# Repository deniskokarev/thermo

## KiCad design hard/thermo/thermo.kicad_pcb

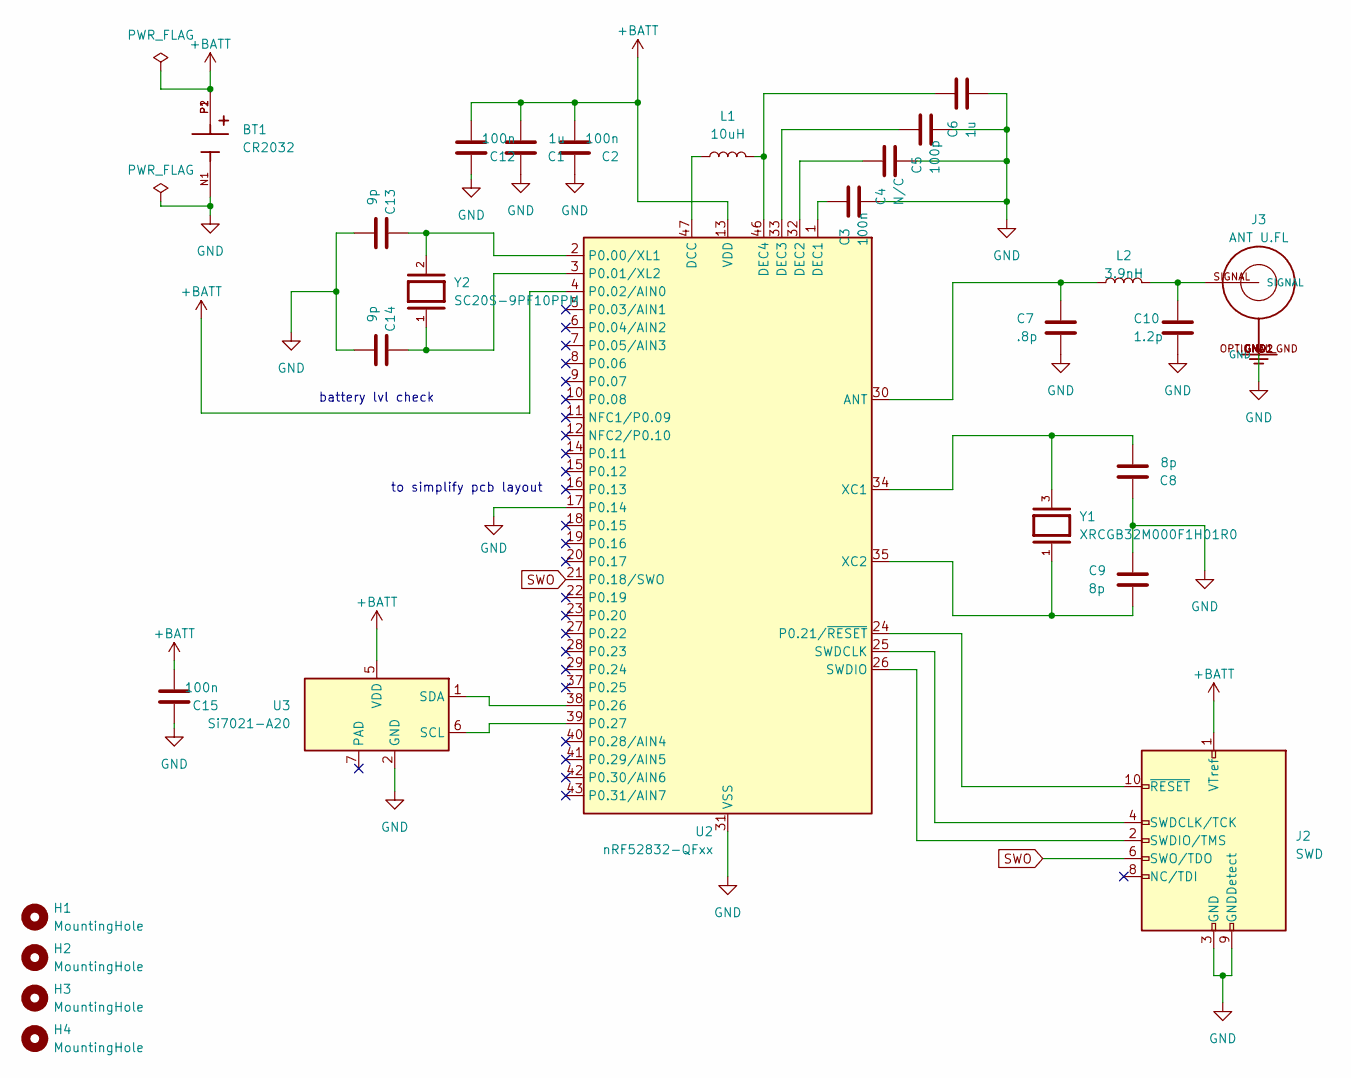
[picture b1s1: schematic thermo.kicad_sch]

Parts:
BT1: CR2032; BAT_BAT-HLD-001
C1, C6: 1u; C_0603_1608Metric_Pad1.08x0.95mm_HandSolder
C2, C3, C12, C15: 100n; C_0603_1608Metric_Pad1.08x0.95mm_HandSolder
C4: N/C; C_0603_1608Metric_Pad1.08x0.95mm_HandSolder
C5: 100p; C_0603_1608Metric_Pad1.08x0.95mm_HandSolder
C7: .8p; C_0603_1608Metric_Pad1.08x0.95mm_HandSolder
C8, C9: 8p; C_0603_1608Metric_Pad1.08x0.95mm_HandSolder
C10: 1.2p; C_0603_1608Metric_Pad1.08x0.95mm_HandSolder
C13, C14: 9p; C_0603_1608Metric_Pad1.08x0.95mm_HandSolder
H1, H2, H3, H4: MountingHole; MountingHole_2.2mm_M2
J2: SWD; PinHeader_2x05_P1.27mm_Vertical_SMD
J3: ANT U.FL; AMPHENOL_A-1JB
L1: 10uH; L_0603_1608Metric_Pad1.05x0.95mm_HandSolder
L2: 3.9nH; L_0603_1608Metric_Pad1.05x0.95mm_HandSolder
U2: nRF52832-QFxx; QFN-48-1EP_6x6mm_P0.4mm_EP4.6x4.6mm
U3: Si7021-A20; DFN-6-1EP_3x3mm_P1mm_EP1.5x2.4mm
Y1: XRCGB32M000F1H01R0; OSC_XRCGB32M000F1H01R0
Y2: SC20S-9PF10PPM; R_1210_3225Metric

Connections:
+BATT: BT1.P1, BT1.P2, C1.1, C2.1, C12.1, C15.1, J2.1 (VTref), U2.4 (P0.02/AIN0), U2.13 (VDD), U2.36 (VDD), U2.48 (VDD), U3.5 (VDD)
GND: BT1.N1, C1.2, C2.2, C3.1, C4.1, C5.1, C6.1, C7.1, C8.2, C9.2, C10.1, C12.2, C13.1, C14.1, C15.2, J2.3 (GND), J2.5 (GND), J2.9 (GNDDetect), J3.GND1 (GND), J3.GND2 (GND), J3.OPTIONAL_GND (GND), U2.17 (P0.14), U2.31 (VSS), U2.45 (VSS), U2.49 (VSS), U3.2 (GND)
unnamed: C10.2, J3.SIGNAL, L2.2
unnamed: J2.4 (SWDCLK/TCK), U2.25 (SWDCLK)
unnamed: J2.2 (SWDIO/TMS), U2.26 (SWDIO)
unnamed: J2.10 (~RESET), U2.24 (P0.21/~RESET)
unnamed: C7.2, L2.1, U2.30 (ANT)
unnamed: L1.1, U2.47 (DCC)
unnamed: C3.2, U2.1 (DEC1)
unnamed: C4.2, U2.32 (DEC2)
unnamed: C5.2, U2.33 (DEC3)
unnamed: C6.2, L1.2, U2.46 (DEC4)
unnamed: C13.2, U2.2 (P0.00/XL1), Y2.2
unnamed: C14.2, U2.3 (P0.01/XL2), Y2.1
unnamed: U2.38 (P0.26), U3.1 (SDA)
unnamed: U2.39 (P0.27), U3.6 (SCL)
unnamed: C8.1, U2.34 (XC1), Y1.3
unnamed: C9.1, U2.35 (XC2), Y1.1
SWO: J2.6 (SWO/TDO), U2.21 (P0.18/SWO)

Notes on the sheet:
battery lvl check
to simplify pcb layout

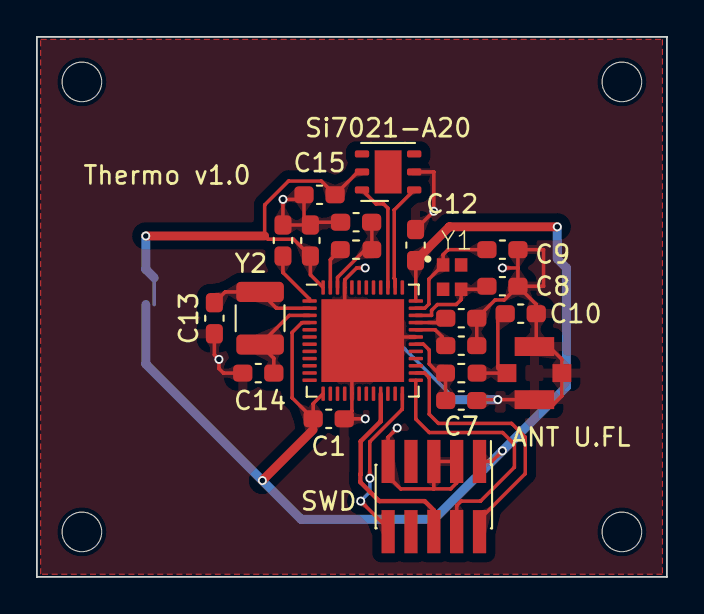
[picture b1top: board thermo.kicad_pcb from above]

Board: 2 copper layers, 35.0 x 30.0 mm, 27 parts (1 on the bottom side), 19 nets.

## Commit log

2023-12-23 initial checkin
2023-12-23 modified readme
2023-12-23 adding CLion files
2023-12-24 working temperature/humidity sensor!
2023-12-24 clion workspace changes
2023-12-24 adding schematics
2023-12-25 first pcb layout
2023-12-25 - don't bother with >3.6V batt input - final layout
2023-12-25 silk screen touch-ups
2023-12-25 - adding 3D models for nRF chip and Battery holder - stop tracking fp-info-cache file
2023-12-25 add thermo.c module
2023-12-25 Gerber files for JLCPCB order
2023-12-26 ignoring CLion workspace.xml file
2023-12-26 adding battery measurement
2023-12-26 removing workspace.xml from git repo
2023-12-26 add BT DIS service
2023-12-26 implementing basic ESP profile. READ works fine, alas NOTIF is not yet
2023-12-26 notifications work too, although simulteoneously, both temp and humidity
2024-01-14 "therm" board definition and validated: - Segger RTT - BT works - ADC works - Temp/Humidity sensor TODO: - settings
2024-01-18 use Settings and Enable DCDC
2024-01-19 reduced power consumption by 1000 :-) 5uA should be good to run for ~3years on CR2032 coin cell batt
2024-03-10 adding Android client
2024-03-10 Dashboard->Devices
2024-03-10 adding devices dynamically
2024-03-10 minor layout tweaks
2024-03-14 adding ViewModels and DeviceDb
2024-03-14 remove DevicesViewModel
2024-04-20 android creating common db interface
2024-04-21 android ble permissions handling added
2024-04-21 ble permissions and scanning
2024-04-21 fw adding ESS service UUID to adv packet
2024-04-21 android ble scanning filter and progress spinner
2024-11-02 make firmware Zeph 3.7 compatible
2024-11-10 starting CI/CD scripts
2024-11-10 [experimental] client changes
2024-11-18 ansible playbook to configure zephyr
2024-11-18 CI ansible don't use handlers
2024-11-20 CI fw build role
2025-01-05 add android sdk role
2025-01-05 bump vm disk usage to 20GB
2025-01-05 fixing android_sdk role
2025-01-05 build android client
2025-01-05 remove cockpit activation
2025-01-05 build firmware
2025-01-23 fist version of mkvm_qemu
2025-01-23 mkvm_qemu seems to work
2025-01-23 mkvm_qemu final touches
2025-01-23 more vm qemu fixes
2025-01-25 add .clangformat
2025-01-26 add dev board
2025-01-26 use C++ with exceptions
2025-02-01 add basic unit tests
2025-02-01 oops, forgot to enable twister test
